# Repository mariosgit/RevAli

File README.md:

# RevAli

Reverse engineered and reviewed tech stuff from a big far east sales thing.

I see if it works and how it can be hacked.. Is it any good. I find out so you don't have to.

| Thing | Image |
|---|---|
| ADAU1452 + AD1938 board bundle <br><br> One of the more excessive investments you can do on AliEx. For around 75-110 bugs <br> you get a nice DSP and CODEC to play with. You might need the overpriced USBi too if you do not have one. The DSP runs some preprogrammed stuff which is kind'a useless but you can hook it up to SigmaStudio right? We will see how easy this is. <br> [ADAU1452+AD1938](ADAU1452_AD1938_Thing/README.md) | {height=100}
 |

| If you like this sort of content or if its been even usefull to you, feel free motivating me publishing such stuff. |  |
|---|---|

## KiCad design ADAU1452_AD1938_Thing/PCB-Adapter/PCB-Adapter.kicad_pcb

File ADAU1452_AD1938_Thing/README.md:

Reverse Engineering some AliEx Products...

# ADAU1452 + AD1938

| This was 3 days of brainfuug, feel free motivating me publishing such stuff. |  |
|---|---|

## ADAU1452 board

### Specs

Power consumption (ADAU+AD1839) 466mA @ 5V

[SPI Flash mem](http://www.zettadevice.com/upload/file/20150821/DS_Zetta_25Q16_RevA_20171120.pdf) "25Q16" is a 16Mbit thing which looks pretty standard.

[Here are some images](IMAGES.md) of the board layouts, that's all you get but it is almost as good as a schematic.

### Connections

| Port | Func | Checked ? |
|---|---|---|
| AD2 | Poti | ??? Sort of.. | 
| MP7 | Switch 1 | YES, does things |
| MP6 | Switch 2 |
| MP9 | Switch 3 |
| | |
| MP11 | Blue | YES |
| MP12 | Red | YES | 
| MP13 | Green | YES |

### Programming Experience

Things I did first:
* Solder in the useless selfboot jumper and set it to not self boot. (Because I managed to "clear" the flash and it started something strange) So now after power up, not much happens (LED goes on dimmed ? Which outputs are on MP11-13? Thats all LRCLK-In[1-3] ok then this should duty cycle somehow.)
* Removed the Jumper on the CODEC in hope to get this into some kind of 48kHz TDM mode.

Mhm yes SigmaStudio managed to download a programm via SPI. It lights up the LEDs and produces distorted audio.

Did not figure out the correct I2S port settings. DAC seems to do after setting it to LeftJustified format.. Is that because the CODEC register 0x02 was set to 0x44 - it's a SDATA offset of 0 ?? Why ??? Is I2S bad?

Getting the CODEC to work with these settings...
* CLOCK_CONTROL / M for Clock Gen 1: 6

* SERIAL_PORTS 

Witing to Flash mem failed at first but is doing things anyway ? Unable to boot usefull stuff. Original content seems to be gonesky.

#### Progress 1.

* Configured the TOS SPDIF input, this can be read in the 1452 EVAL board docu by ADI. This works. 
* Aaaand it outputs to the DAC. Buuuuut, with full volume it distorts ! Is that an analog problem ??? So without the 

#### Todo

* Program SPI FLASH !?

## CODEC AD1938

This needs the 3.3V from the DSP board because it does not have it's own regulator.

In the **default setting** with the mode jumper at 2-3 position this will be configered to
* 192kHz TDM mode.
* No BitClock (BCLK) needed, the internal PLL is set to generate a master clock from the DLRCLK signal.

### Setup 

The CODEC board has a 8 pin MCU (STC15W101 Vcc@2 Gnd@4) on it, which sends init data to the CODEC. It reads the jumper position (2 bits ? or analog values ? No more likely 2 bits with pullups, pin 3 is GND) and then adjust what it's writing...  Here is the data...

The CODEC is set up by writing 24bit sequences over it's control SPI port. 
1. byte is the ```chip address << 1 | R/W``` this is allways 0x08 for writing access
2. byte is the register address to write
3. byte is data

(I skip adr 06-0D these are the DAC attenuators, allways set to 0)

Column 1 is the plain data which is send when jumper is at 2-3 (default position, TDM 192kHz)
Column 2 is the difference in data when jumper is removed (48kHz TDM?)
Column 3 is the difference when all are connected = all grounded. TODO!

| ChipAdr RegisterAdr Data (2-3) | data (open) | [1-2-3] | Reg Name | Meaning |
|---|---|---|---|---|
| 08 00 BE |    | | PLL0 | PLL=on, INPUT 768 ???, XTAL=off, pllsrc=DLRCLK, ADC,DAC=on <br>(PLL is set to follow the LRCLK, no BCLK signal is needed.) |
| 08 01 F8 |    | | PLL1 | DAC+ADC clk src = PLL, volt ref = on
| 08 02 44 | 40 | | DAC0 | 192(48)khz, SDATA offset to the LR to 0 !!! (Left justified ?), TDM
| 08 03 0E | 0C | | DAC1 | Slave, BCLK from BCLK pin???, BCLK pol = "normal", LRpol=left high, BCLK per frame 512 (256) Haeh???
| 08 04 C0 |    | | DAC2 | 24bit non inverted
| 08 05 00 |    | | DAC MUTE | = Unmute all |
| 08 0E 80 | 00 | | ADC0 | Sample Rate 192 (48), unmute
| 08 0F A0 |    | | ADC1 | TDM 24bit SDATA offset = 1 !!! Ahhh Why
| 08 10 36 | 26 | | ADC2 | LR=50/50, BCLK-rising edge, LR=Left high, Slave, BCLK per frame 256 (128), CLK source = BCLK !!! Haehhh?
| | | |

Hmm some values look kind'o messi. Would I like to unsolder that chip and ground all control pins to get the default config ??? I think then it needs a MCLK, which is not on the board. :-( the ADI eval board the ctl pins all grounded and MCLK is driven by MCLK out from the DSP. This could work.

### Analog Problem ?

CODEC docs say: Full-Scale Output Voltage 0.88 Vrms (2.48 Vp-p). What comes out then ? Meassuring... so I added an Signalsource which outputs a sinus with 1kHz @ 0db - should draw a nice sinus with 2.48Vpp at the output right ?

| | What | Value |
|---|---|---|
| DAC out | Vp-p | 1.94 V |

Looks exactly like a sinus right? GRRR what the hack...

.png)

Pin FILTER (35) is a foltage reference. 1.5V
Pin CM (38) .. can be used to bias external opamps... 1.5V
Both are second pin at the 36 edge. It goes onto the 4 caps next to this edge.

The OpAmps seem to run on 5V ? Mhm The neg power rail goes onto that backside T rail which is visible from the below.

The PCB is not quite what the picture shows, the new one has WQFN opamps and bit less jumperstuff near the USB port.

Here is a tl072 for reference

How the out stage should look like...

The OpAmp circuit is similar to the official EVAL board.. FILTER and CM pins have 1.6V, DAC outputs are 1.5V Should be ok, right ?

#### OpAmps ?

Installed ones: WQFN marking: ```ovii TI541```  or  ```OVII TI521``` ???

Replaced with MCP6002 RailToRail types, **works**. :-P

### Problems ?

* CODEC Will not always start up.

# Moans and Nickls !?

The boards for CODEC and DSP have different sizes, yeah who needs casing anyway.

CODEC OpAmps run on the main and only 5V rail !? It's noisy isn't it.

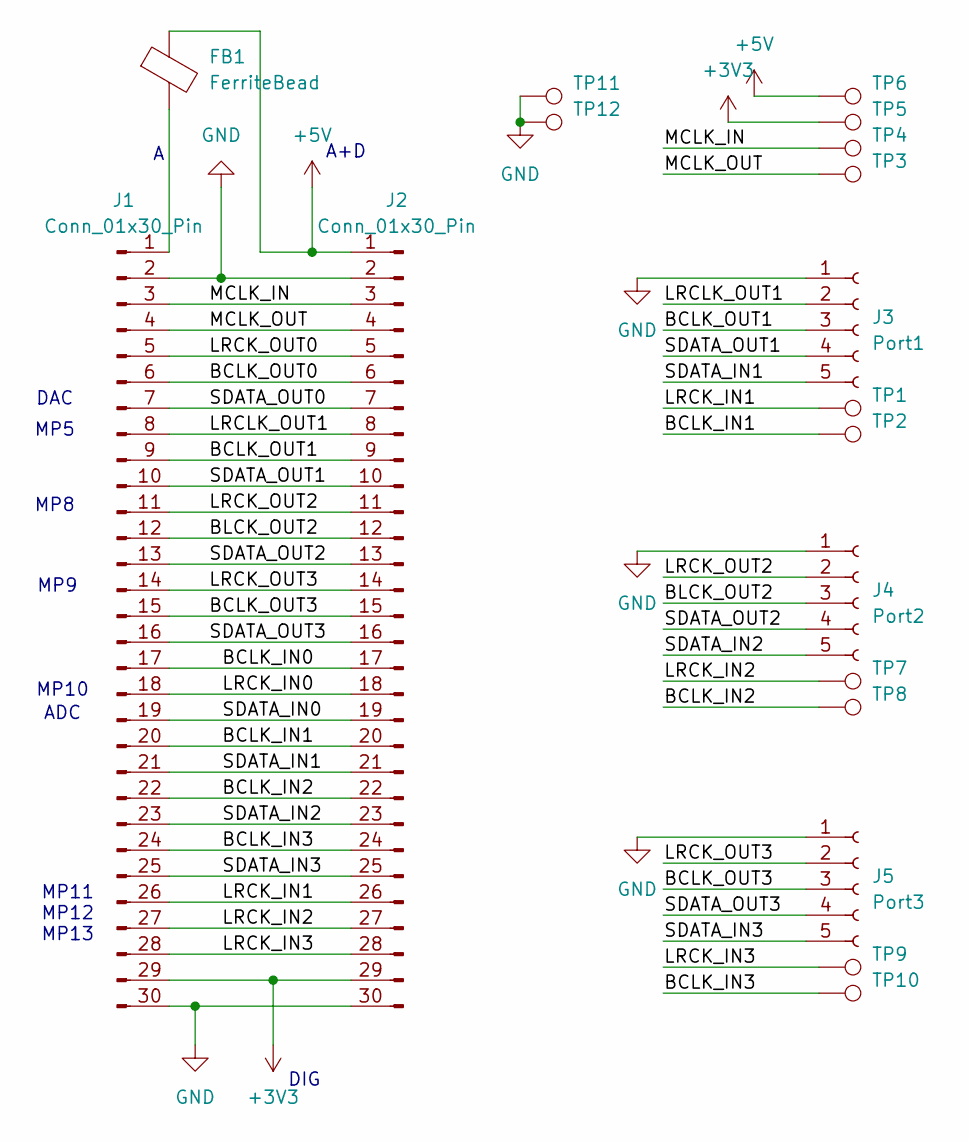
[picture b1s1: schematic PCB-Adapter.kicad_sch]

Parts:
FB1: FerriteBead; L_0603_1608Metric_Pad1.05x0.95mm_HandSolder
J1, J2: Conn_01x30_Pin; PinHeader_1x30_P2.00mm_Vertical
J3: Port1; PinHeader_1x05_P2.54mm_Vertical
J4: Port2; PinHeader_1x05_P2.54mm_Vertical
J5: Port3; PinHeader_1x05_P2.54mm_Vertical
TP1, TP2, TP3, TP4, TP7, TP8: TestPoint; TestPoint_Pad_2.0x2.0mm
TP5, TP6, TP9, TP10, TP11, TP12: TestPoint; TestPoint_Loop_D2.50mm_Drill1.0mm

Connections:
+3V3: J1.29, J2.29, TP5.1
+5V: FB1.1, J2.1, TP6.1
/BCLK_IN0: J1.17, J2.17
/BCLK_IN1: J1.20, J2.20, TP2.1
/BCLK_IN2: J1.22, J2.22, TP8.1
/BCLK_IN3: J1.24, J2.24, TP10.1
/BCLK_OUT0: J1.6, J2.6
/BCLK_OUT1: J1.9, J2.9, J3.3
/BCLK_OUT3: J1.15, J2.15, J5.3
/BLCK_OUT2: J1.12, J2.12, J4.3
/LRCK_IN0: J1.18, J2.18
/LRCK_IN1: J1.26, J2.26, TP1.1
/LRCK_IN2: J1.27, J2.27, TP7.1
/LRCK_IN3: J1.28, J2.28, TP9.1
/LRCK_OUT0: J1.5, J2.5
/LRCK_OUT2: J1.11, J2.11, J4.2
/LRCK_OUT3: J1.14, J2.14, J5.2
/LRCLK_OUT1: J1.8, J2.8, J3.2
/MCLK_IN: J1.3, J2.3, TP4.1
/MCLK_OUT: J1.4, J2.4, TP3.1
/SDATA_IN0: J1.19, J2.19
/SDATA_IN1: J1.21, J2.21, J3.5
/SDATA_IN2: J1.23, J2.23, J4.5
/SDATA_IN3: J1.25, J2.25, J5.5
/SDATA_OUT0: J1.7, J2.7
/SDATA_OUT1: J1.10, J2.10, J3.4
/SDATA_OUT2: J1.13, J2.13, J4.4
/SDATA_OUT3: J1.16, J2.16, J5.4
GND: J1.2, J1.30, J2.2, J2.30, J3.1, J4.1, J5.1, TP11.1, TP12.1
unnamed: FB1.2, J1.1

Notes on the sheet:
MP11 MP12 MP13
MP5
MP8
DIG
MP9
MP10
DAC
ADC
A+D

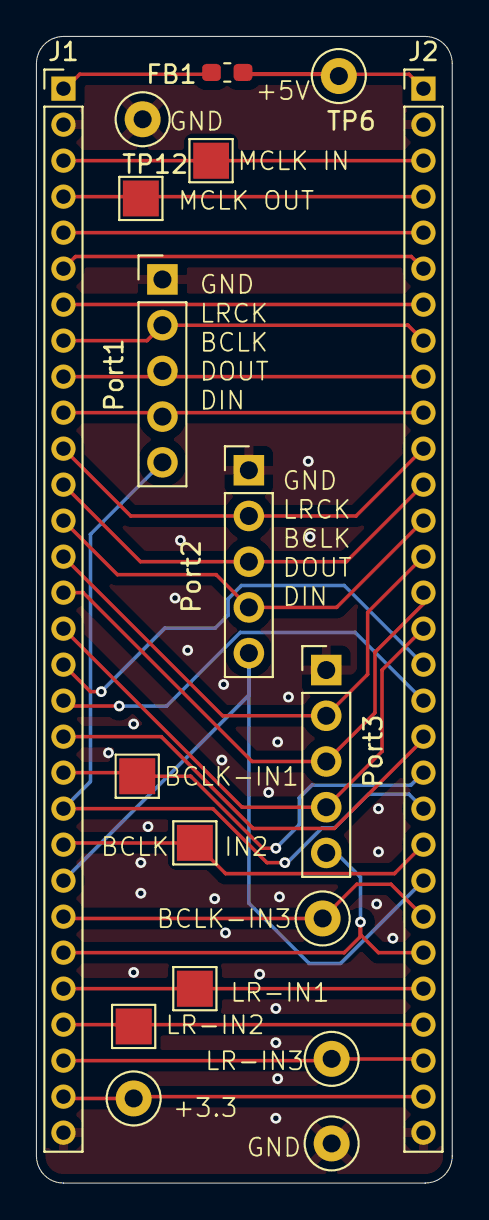
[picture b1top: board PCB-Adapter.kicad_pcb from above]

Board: 2 copper layers, 23.1 x 63.7 mm, 18 parts (0 on the bottom side), 30 nets.

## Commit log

2024-07-08 Initial commit.
2024-07-27 Added breakout PCB.
